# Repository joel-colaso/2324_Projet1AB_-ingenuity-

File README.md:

# ReadMe

Mars 2020 est une mission spatiale qui consiste à déployer l'astromobile (rover) Perseverance sur le sol martien pour étudier sa surface et collecter des échnatillons du sol. Elle constitue la première d'une série de trois missions dont l'objectif final est de ramener ces échantillons sur Terre pour leur analyse. 

Ingenuity est un petit hélicoptère développé par l'agence spatiale Américaine, la NASA. Il est mis en oeuvre à titre expérimental sur le sol de la planète Mars au cours de la mission Mars 2020.
L'hélicoptère est embarqué à bord du rover Perseverance. 

Le 19 avril 2021, pour la première fois dans l'histoire de l'ère spatiale, un engin effectue un vol motorisé dans l'atmosphère ténue d'une autre planète. L'objectif d'Ingenuity est la reconnaissance optique du terrain, l'hélicoptère réalise de nombreuses photos aériennes utiliées par les pilotes de l'astromobile Perseverance pour identifier les obstacles et les sites prometteurs (prelèvement d'échantillons rocheux sur le sol martien). 

Ingenuity est un hélicoptère de 1,8 kg disposant de 2 rotors contrarotatifs coaxiaux. Il tire son énergie de 6 batteries lithium-ion rechargées par des cellules solaires. Son système de navigation lui permet de suivre sans intervention humaine un trajet pré-programmé. Sa seule charge utile est une caméra. 

La mission s'est récemment arrêtée (18 janvier 2024) en raison de la casse d'un pale lors du 72e vol. 

Ingenuity a ouvert de nouvelles perspectives pour l'exploration de Mars. La NASA et l'ESA, dans leur mission de retour d'échantillons martien, incluent maintenant 2 hélicopères similaires qui seront chargés de collecter les tubes contenant les échantillons martien déposés par l'astromobile Perseverance en cas de panne de celui-ci. 

Dans  ce projet, nous allons tâcher de reproduire le module Ingenuity. 

# Notre Projet
Notre projet est donc d'essayer de réaliser cet hélicopètre en mode miniature. C'est à dire que l'on veut créer un véhicule pouvant se déplacer dans les airs et prendre une photo de ce qu'il se passe en dessous. Pour  ela, nous disposons d'un total de 10 séances où nous devrons mélanger PCB, codage, soudage, etc.

# Equipe
Pour ce projet notre équipe est composée de quatres élèves en première années d'écoles d'ingénieur : l'ENSEA. Il est important de souligner ici que certains membres de ce projet sont passionnés par l'aérospatial, ce qui donc motive d'avantage ce dernier. Étant tous différents, nous disposons donc de compétences variées. Entre autres quand certains codent, d'autres s'occupent de la soudure ou de la réalisation du PCB. 

# Journal de bord
C'est ici que nous résumerons, séance par séance les avancées du projet. 

## Séance 1
### Réflexion autour du projet : documentation
Alors que nous avions directement l'idée d'Ingenuity, il est important de savoir où nous nous aventurons. Nous nous sommes donc renseignés sur les hélicoptères de base, puis sur ceux mono-axe, pour enfin lire diverses documentations sur le véhicule de la NASA.
Ensuite, est venu le temps des questions plus détaillées : comment peut-on le refaire ? Quels moteurs ? Combien ? Doit-on utiliser un seul axe ou plusieurs ? Comment le faire avancer/reculer ? Etc.

## Séance 2
### Premiers détails : Schémas et Cahier Des Charges
Lors de cette deuxième séance, nous avons concrétisé nos découvertes. Nous nous sommes principalement basés sur des schémas, plus ou moins vulgarisés. C'est donc lors de celle-ci que notre schéma d'architecture a commencé à prendre forme.

De plus, nous avons réfléchi à comment faire avancer notre hélicoptère. La question se pose ici, car en réalité, les pâles s'inclinent vers la direction souhaitée, ce qui n'était pas réalisable pour nous car il nous aurait fallu imprimer des pièces de taille bien trop petites, ou bien trop compliquées à souder par la suite. Nous devions donc réfléchir à une alternative. C'est ainsi que nous avons eu l'idée d'un poids se baladant dans la coque de notre hélicoptère. Ce dernier incline en réalité tout l'hélicoptère et non seulement les hélices.
Enfin, afin de conclure cette séance productive, nous avons tout juste débuté le schéma d'architecture de notre système.
(Tous les documents cités sont également disponibles sur le git dans le dossier "Schematics").

## Séance 3
### Schéma d'Archi : un pas important
Lors de cette troisième séance, nous nous sommes principalement concentrés sur le schéma d'architecture et tout ce qui l'entoure. Nous avons donc recherché avec plus de détails quels composants nous allions utiliser (transistor, régulateur de tension, ...) et une fois trouvés, nous avons fouillé afin de trouver leur datasheet respective. C'est donc ici que notre liste des composants nécessaires a commencé à prendre forme. Entre les résistances, les capacités et les connecteurs, la liste peut sembler longue.

En somme, nous avons donc finalisé le schéma d'architecture puis rassemblé au sein d'un document tous les composants nécessaires à notre projet. À la fin de cette séance, nous avons d'ailleurs commandé ceux que nous n'avions pas à notre disposition.

## Séance 4
### PCB et codage 
Quatrième semaine de projet, début de la réalisation du PCB de notre hélicoptère. Notre schéma d'architecture étant fini et validé par notre encadrant, nous pouvons donc passer à la réalisation de notre PCB. Dans un premier temps, nous avons donc juste retranscrit notre schéma d'architecture sur un schéma PCB en liant nos différents composants électroniques avec leurs entrées et sorties respectives. 

Cepednant, pour faire cela, il y a certains éléments dont nous avons du faire l'empreinte nous même tel que LDO que nous utilisons car il étati indisponible sur KiCAD. 

Au niveau du codage, nous avons juste continué à prendre en main le servo moteur à base de vidéos youtube et différents tests comme simplement lui faire faire des aller-retours. 

## Séance 5
### Routage et toujours codage
Le schéma du PCB est terminé, il ne nous reste plus que la dernière étape, aussi fastidieuse soit elle : celle du routage. Notre objectif est le suivant : optimiser au mieux la place ainsi que la masse. En effet, il ne faut pas que notre hélicopètre ne pèse trop lourd, il ne décollerait donc pas du sol. 

Le PCB est donc prêt à être envoyé à l'usinage, c'est donc ce que nous faisons et il ne nous restera plus que la soudure à faire. Il ne reste plus qu'à attendre sa réception maintenant. 

Pour le codage, cette fois les servomoteurs tournent cette fois-ci bien. Désormais, nous nous attaquons à la commande de l'angle de ces derniers. Pour cela, nous créons des fonctions prenant comme paramètre l'angle.  

## Séance 6
### Soudure, Github et encore du codage...
La moitié des séances ont été faites, et nous voyons de plus en plus notre projet se concrétiser malgré une certaine crainte sur le temps nous restant. Maintenant, on a reçu notre PCB, nous allons donc souder tous nos composants dessus. Pour cela, deux des membres de notre projet s'en occupe, l'un soude pendant que l'autre lui indique les directives (quel élément placé et où). Pour cela, ces deux derniers s'appuient beaucoup sur le BOM proposé par KiCAD. 

[INSERER BOM]

Au niveau du codage, les deux autres membres s'entraident afin d'améliorer au mieux nos fonctions et donc d'optimiser le temps d'éxécution. Les fonctions sont donc créées permettant à un servomoteur de tourner jusqu'à un certain angle donné. 

De plus, le git a été mis à jour car jusque maintenant, on n'uploadait nos divres fichiers et non les pushait. Ainsi, nous avons donc appris à se servir de git dans l'objectif de ne plus jamais upload et juste push.

## Séance 7
### Fin de la soudure, Reflexion sur le montage, mise en page et puis ... du codage
Lors de la dernière séance, un nous avions soudé un élément qui n'était pas le bon. Ainsi, nous avons du le désouder pour resouder le bon cette fois-ci. 

Suite à ça, nous avons encore une fois divisé le travail en deux équipes différentes. Une s'occupaient de continuer le codage pendant que l'autre commençait la modélisation (puis l'impression) 3D de toute la structure de notre Ingenuity. Nous avons donc imprimé au total une base inférieure carrée, quatres pattes permettant de le voir se poser ainsi qu'une base supérieure. Nous nous sommes très fortement inspiré du vrai véhicule de base quant à sa structure. 

Ensuite est venu une reflexion importante, si ce n'est nécessaire pour faire se déplacer notre véhicule dans toutes les directions possibles et non juste diminuer et monter en altitude. Ainsi, nous avons eu ensemble l'idée d'un système de "balancier" s'appuyant beaucoup sur le centre de gravité de ce dernier. Nous plaçons une masse qui selon sa position par rapport à ce dernier le fera se déplacer. Entre autres, si le masse se situe au nord du centre de gravité, alors l'hélicoptère avancera. Alors que s'il se situe à sa droite, l'hélicoptère se déplacera vers .... la droite. 

[Insérer schéma masses déplacement]

Il faut donc désormais concrétiser cette reflexion et coder ce qui va avec. Nous avons donc coder six fonctions différentes : Nord-Ouest, Sud-Ouest, Sud, Sud-Est, Nord-Est et Nord. Selon la fonction, l'angle des servomoteurs est différents. Voici quelques exemples : 

[Inserer schéma Nord-Ouest, Sud]

De plus, on décide d'à partir de cette séance de mettre en place une to-do-list (que voici ci-dessous), dont nous monterons l'avancée lors des séances suivantes. 

    * Coder relation Rasberry - STM
    * Coder Rasberry pour prendre une photo
    * Coder moteurs 
    * Monter le véhicule 
    * Le faire voler

## Séance 8
### Réflexion sur l'architecture du code, poursuite du codage et Fin de l'impression des pieces en 3D
Dans un premier temps, nous avons vérifié que notre PCB fonctionne correctement en le branchant à un PC sur STM32CubeIDE en sélectionnant le bon microprocesseur. Les LEDs placés lors de la création de notre PCB s'allument bien, ce qui montre que le PCB fonctionne effectivement correctement.

Ensuite, nous avons réflechi à une architecture pour le code. Le tout en différenciant bien les difféfents fichiers .py et .c. Puisque nous rappelons qu'ici nous aurons besoin des deux langages de codage, l'un pour le microprocesseur et l'autre pour la Rasberry Pi0. 
Schéma d'architecture du code en python pour la Raspberry Pi et en language C pour le reste des fichiers :

Puis, il était nécessaire de créer une machine à états au sein de notre code. Ainsi, afin d'attaquer au mieux cette partie, nous l'avons réaliser dans un premier temps à l'aide d'un schéma.
Schéma de la machine à état du fichier Instructions.py de l'architecture du code :

De plus, nous avons réussi à connecter la caméra à la RPI0 et donc ensuite à prendre des photos avec. Le code pour cette action a bien été écrit et éxécuté, c'est donc une de nos fonctionnalités qui est désormais en place. Puis nous avons avancé sur le code en C. Et puisque l'on parle de réussite, nous avons testé si notre PCB était bel et bien fonctionnel. Et en effet, il était bel et bien fonctionnel !

Pour conclure cette séance, nous avons continué les impressions 3D pour avoir le corps de notre drone Ingenuity, une petite boite avec des trous en dessous pour la camera et pour l'altimètre infrarouge. Nous commencerons le collage de toute les parties lors de la prochaine séance ainsi que l'assemblage des differentes pièces electroniques.

## Séance 9
### Présentation et derniers apports
Avant dernière séance, et pas des moindres. Lors de celle-ci, nous avons commencé par la présentation de notre projet à l'oral devant tout notre groupe ainsi que notre professeur référent. Nous avons dans un premier temps parler de la mission Mars 2020 de la NASA pour introduire notre projet. Puis nous avons expliqué étape par étape (comme le fait ce compte-rendu séance par séance) comment nous fonctionnions au sein de ce dernier. 

[Projet 1A - Ingenuity.pptx](https://github.com/joel-colaso/2324_Projet1AB_-ingenuity-/files/15461084/Projet.1A.-.Ingenuity.pptx)

Une fois ceci fait, il fallait nous hater à terminer (ou du moins avancer le plus possible) notre projet puisque notre démonstration a lieu le lendemain, et pour l'instant notre véhicule ne décole pas. Alors nous avons comme d'habitude diviser le groupe, pendant que deux finissait les impressions 3D et commencer à monter la "coque" du véhicule, deux autres codaient. L'un s'occupait de finir le programme permettant de faire tourner les deux moteurs (langage C) pendant que l'autre s'occupait de finir le code permettant la liaison de la RPI0 à notre processeur STM32 (langage Python)

À la toute fin de la séance, le code python était terminé, nous pouvions donc commander notre hélico en lui disant dans quelle direction il devait se dirigier (Nord, Sud, Est ou Ouest) mais aussi si l'on voulait prendre une photo avec la caméra implémentée. 

## Séance 10
### Dernières modifications et démonstration 
Dernière séance, nous devons faire en sorte que notre hélicoptère vole aujourd'hui. Malgré des efforts acharnés de tous les côtés, ils ne décolle pas pour plusieurs raisons : manque de code, mais aussi trop lourd. On reste donc sur un échec mais qui nous a apprit énormément de choses. Nous sommes fiers et heureux de pouvoir reprendre ce projet l'année prochaine afin de cette fois-ci, le terminer et le faire se déplacer. 

# Livrables
## PCB
Voici une capture d'écran de notre PCB une fois routé. On reconnait bien les différentes parties que nous avons prit le soin de nommer. 

## Code
Même si ce dernier n'est pas fini, nous avions probablement le plus important : l'architecture. 

## A l'année prochaine !

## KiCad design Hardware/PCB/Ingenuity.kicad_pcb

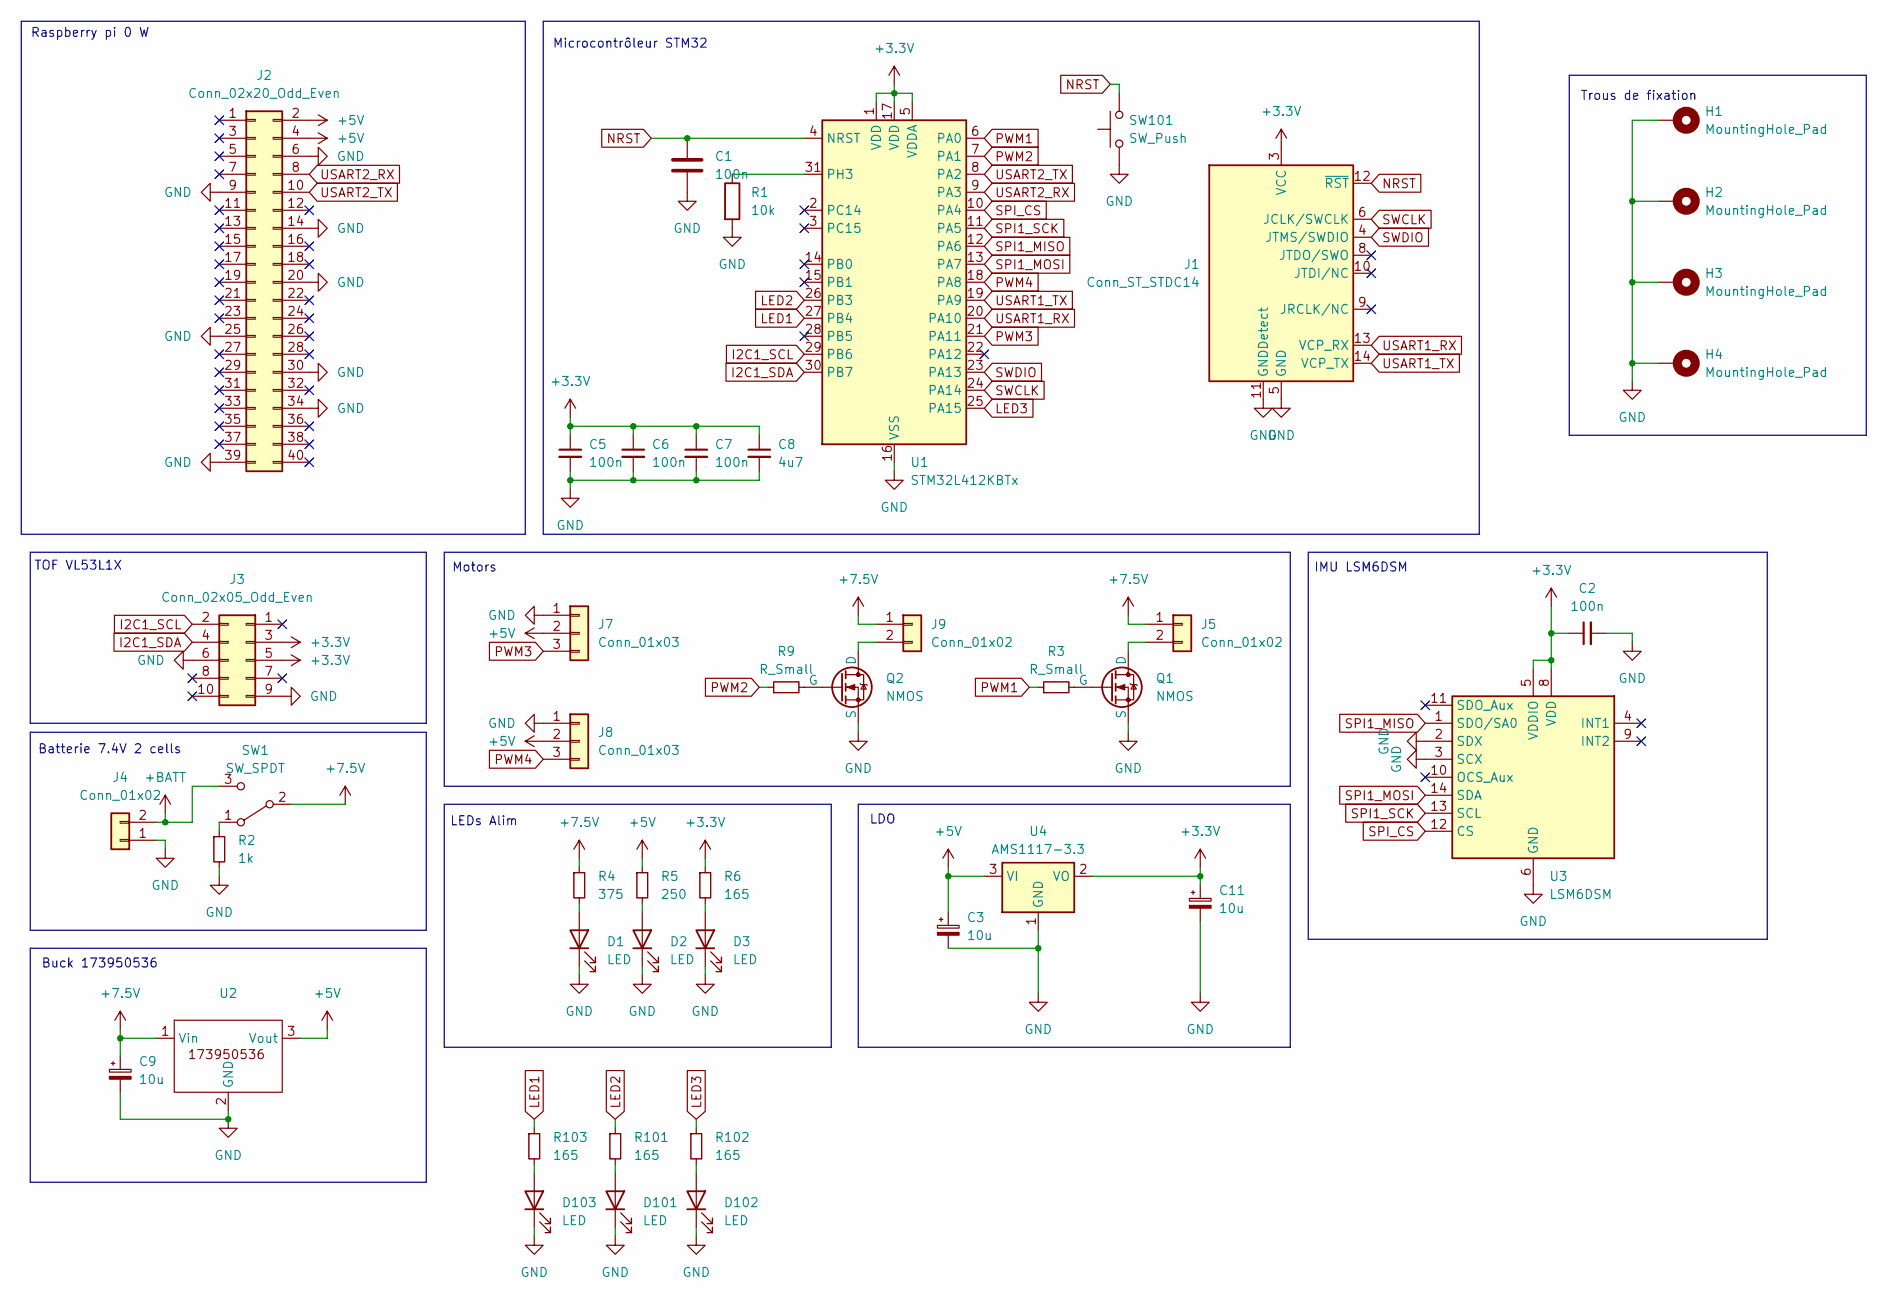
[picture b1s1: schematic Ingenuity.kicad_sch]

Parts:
C1, C2, C5, C6, C7: 100n; C_0402_1005Metric
C3, C9, C11: 10u; C_0603_1608Metric
C8: 4u7; C_0402_1005Metric
D1, D2, D3, D101, D102, D103: LED; LED_0603_1608Metric
H1, H2, H3, H4: MountingHole_Pad; MountingHole_2.7mm_M2.5_DIN965_Pad
J1: Conn_ST_STDC14; PinHeader_2x07_P1.27mm_Vertical_SMD
J2: Conn_02x20_Odd_Even; PinHeader_2x20_P2.54mm_Vertical
J3: Conn_02x05_Odd_Even; PinHeader_2x05_P2.54mm_Vertical
J4, J5, J9: Conn_01x02; JST_XH_B2B-XH-A_1x02_P2.50mm_Vertical
J7, J8: Conn_01x03; JST_XH_B3B-XH-A_1x03_P2.50mm_Vertical
Q1, Q2: NMOS; SOT-23
R1: 10k; R_0402_1005Metric
R2: 1k; R_0402_1005Metric
R3, R9: R_Small; R_0402_1005Metric
R4: 375; R_0402_1005Metric
R5: 250; R_0402_1005Metric
R6, R101, R102, R103: 165; R_0402_1005Metric
SW1: SW_SPDT; SW_472121010111; MPN 472121010111
SW101: SW_Push; SW_Push_1P1T_NO_6x6mm_H9.5mm
U1: STM32L412KBTx; LQFP-32_7x7mm_P0.8mm; MPN STM32L412KBT6
U2: Buck_17395xx36
U3: LSM6DSM; LGA-14_3x2.5mm_P0.5mm_LayoutBorder3x4y
U4: AMS1117-3.3; SOT-223-3_TabPin2

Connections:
+3.3V: C2.1, C5.1, C6.1, C7.1, C8.1, C11.1, J1.3 (VCC), J3.3, J3.5, R6.1, U1.1 (VDD), U1.5 (VDDA), U1.17 (VDD), U3.5 (VDDIO), U3.8 (VDD), U4.2 (VO)
+5V: C3.1, J2.2, J2.4, J7.2, J8.2, R5.1, U2.3 (Vout), U4.3 (VI)
+7.5V: C9.1, J5.1, J9.1, R4.1, SW1.2 (B), U2.1 (Vin)
+BATT: J4.2, SW1.3 (C)
GND: C1.2, C2.2, C3.2, C5.2, C6.2, C7.2, C8.2, C9.2, C11.2, D1.1 (K), D2.1 (K), D3.1 (K), D101.1 (K), D102.1 (K), D103.1 (K), H1.1, H2.1, H3.1, H4.1, J1.5 (GND), J1.7 (GND), J1.11 (GNDDetect), J2.6, J2.9, J2.14, J2.20, J2.25, J2.30, J2.34, J2.39, J3.6, J3.9, J4.1, J7.1, J8.1, Q1.3 (S), Q2.3 (S), R1.2, R2.2, SW101.1, U1.16 (VSS), U1.32 (VSS), U2.2 (GND), U3.2 (SDX), U3.3 (SCX), U3.6 (GND), U3.7 (GND), U4.1 (GND)
I2C1_SCL: J3.2, U1.29 (PB6)
I2C1_SDA: J3.4, U1.30 (PB7)
LED1: R103.1, U1.27 (PB4)
LED2: R101.1, U1.26 (PB3)
LED3: R102.1, U1.25 (PA15)
NRST: C1.1, J1.12 (~RST), SW101.2, U1.4 (NRST)
unnamed: D1.2 (A), R4.2
unnamed: D2.2 (A), R5.2
unnamed: D3.2 (A), R6.2
unnamed: D101.2 (A), R101.2
unnamed: D102.2 (A), R102.2
unnamed: D103.2 (A), R103.2
unnamed: J5.2, Q1.1 (D)
unnamed: J9.2, Q2.1 (D)
unnamed: Q1.2 (G), R3.2
unnamed: Q2.2 (G), R9.2
unnamed: R2.1, SW1.1 (A)
unnamed: R1.1, U1.31 (PH3)
PWM1: R3.1, U1.6 (PA0)
PWM2: R9.1, U1.7 (PA1)
PWM3: J7.3, U1.21 (PA11)
PWM4: J8.3, U1.18 (PA8)
SPI1_MISO: U1.12 (PA6), U3.1 (SDO/SA0)
SPI1_MOSI: U1.13 (PA7), U3.14 (SDA)
SPI1_SCK: U1.11 (PA5), U3.13 (SCL)
SPI_CS: U1.10 (PA4), U3.12 (CS)
SWCLK: J1.6 (JCLK/SWCLK), U1.24 (PA14)
SWDIO: J1.4 (JTMS/SWDIO), U1.23 (PA13)
USART1_RX: J1.13 (VCP_RX), U1.20 (PA10)
USART1_TX: J1.14 (VCP_TX), U1.19 (PA9)
USART2_RX: J2.8, U1.9 (PA3)
USART2_TX: J2.10, U1.8 (PA2)

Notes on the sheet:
Trous de fixation
Motors
LDO
Buck 173950536
Raspberry pi 0 W
IMU LSM6DSM
Batterie 7.4V 2 cells
LEDs Alim
Microcontrôleur STM32
TOF VL53L1X

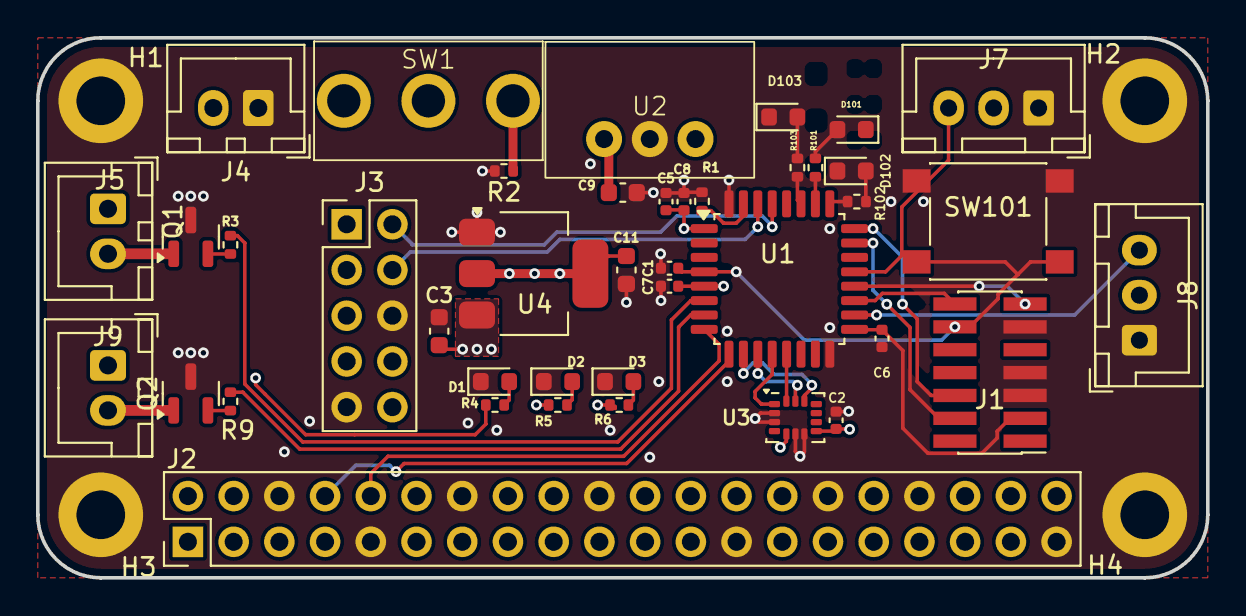
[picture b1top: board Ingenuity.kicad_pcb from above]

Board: 4 copper layers, 65.0 x 30.0 mm, 45 parts (0 on the bottom side), 37 nets.

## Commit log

2024-02-26 Create Compte rendu
2024-02-26 Update Compte rendu
2024-03-01 Rename Compte rendu to Compte_rendu.yml
2024-03-01 Rename Compte_rendu.yml to Compte_rendu.md
2024-03-04 Added Untitled Diagram.drawio
2024-03-04 Ajouté(e) oui.drawio
2024-03-18 update schematic
2024-03-18 Mettre à jour Schema_Archi.png
2024-03-31 update schematic, switch pins, change zones and routing
2024-04-03 add led, button
2024-04-04 finalize pcb
2024-04-22 First Try to commit
2024-04-22 pushed
